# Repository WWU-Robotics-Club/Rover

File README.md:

# Rover

A robotic rover project.

See the wiki for more info: https://gitlab.cs.wallawalla.edu/robotics-club/Rover/-/wikis/home

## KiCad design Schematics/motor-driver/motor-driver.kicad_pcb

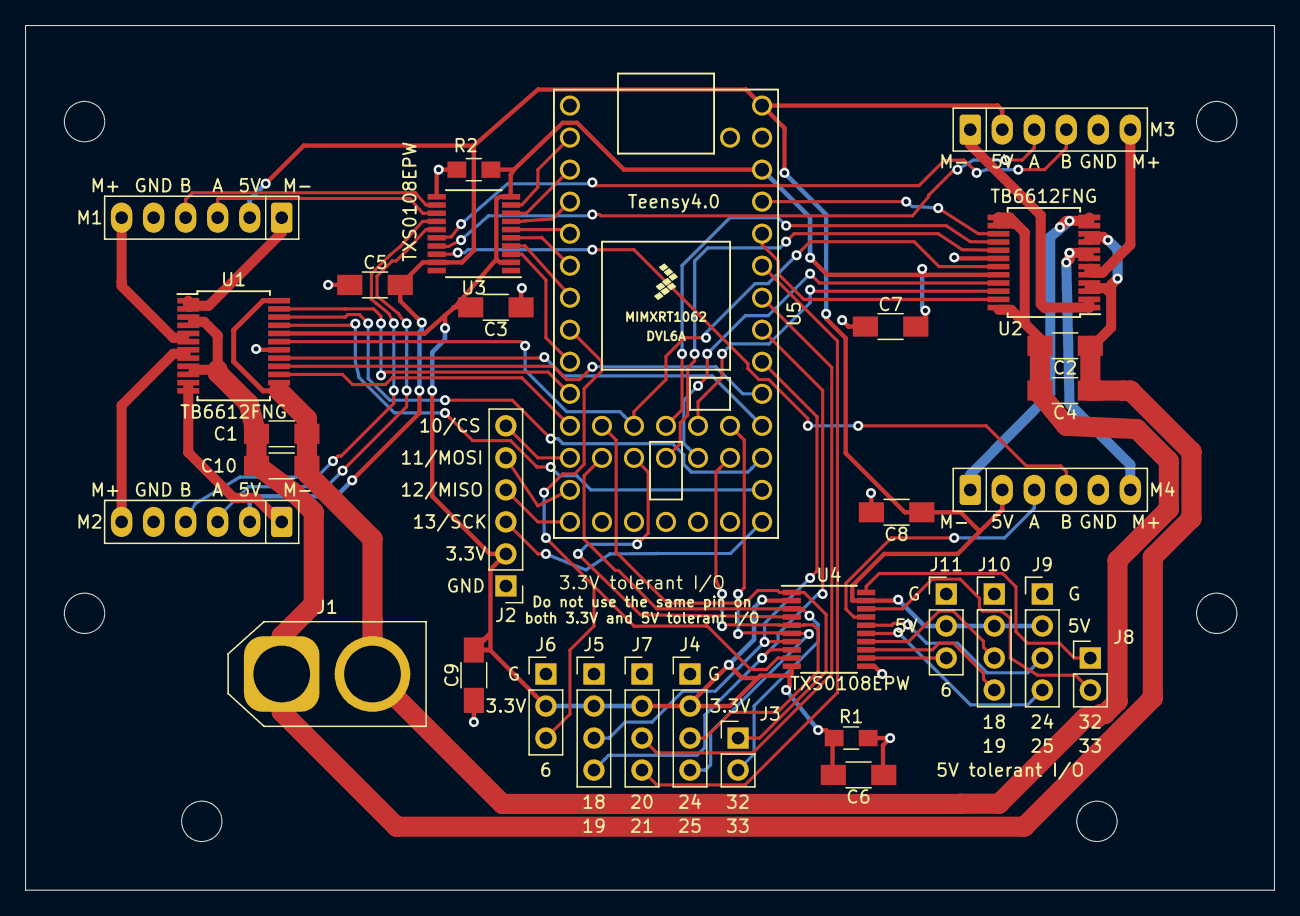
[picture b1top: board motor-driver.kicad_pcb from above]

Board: 2 copper layers, 99.1 x 68.6 mm, 32 parts (0 on the bottom side), 62 nets.

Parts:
C1, C2: 10uF; C_1206_HandSoldering
C3, C4, C5, C6, C7, C8, C9, C10: 0.1uF; C_1206_HandSoldering
J1: XT-60; AMASS_XT60-M_1x02_P7.20mm_Vertical
J2: SPI; SPI_3.3V
J3: 32-33 3.3V; 32-33_3.3V
J4: UART/I2C/PWM 3.3V; UART_I2C_PWM_3.3V
J5: I2C/Ain/PWM 3.3V; I2C_Ain_PWM_3.3V
J6: PWM/PPM 3.3V; PPM_PWM_3.3V
J7: UART/Ain; UART_Ain_3.3V
J8: 32-33 5V; 32-33_5V
J9: UART/I2C/PWM 5V; UART_I2C_PWM_5V
J10: I2C/Ain/PWM 5V; I2C_Ain_PWM_5V
J11: PWM/PPM 5V; PPM_PWM_5V
M1, M2, M3, M4: encoder-motor; Motor_Header_Pitch2.54mm
R1, R2: 47k; R_0805_HandSoldering
U1, U2: TB6612FNG; SSOP-24_5.3x8.2mm_Pitch0.65mm
U3, U4: TXS0108EPW; TSSOP-20_4.4x6.5mm_Pitch0.65mm
U5: Teensy4.0; Teensy40

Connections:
+3V3: C3.2, C6.2, C7.2, C9.2, J2.2, J4.2, J5.2, J6.2, J7.2, R1.1, R2.1, U1.20, U2.20, U3.2, U3.10, U4.2, U4.10, U5.31
+5V: C5.1, C8.1, J9.2, J10.2, J11.2, M1.2, M2.2, M3.2, M4.2, U3.19, U4.19, U5.33
+BATT: C1.2, C2.2, C4.2, C10.2, J1.2, U1.13, U1.14, U1.24, U2.13, U2.14, U2.24
-BATT: C1.1, C2.1, C4.1, C10.1, J1.1, U1.3, U1.4, U1.9, U1.10, U2.3, U2.4, U2.9, U2.10
/M1+: M1.6, U1.5, U1.6
/M1-: M1.1, U1.1, U1.2
/M2+: M2.6, U1.7, U1.8
/M2-: M2.1, U1.11, U1.12
/M3+: M3.6, U2.5, U2.6
/M3-: M3.1, U2.1, U2.2
/M4+: M4.6, U2.7, U2.8
/M4-: M4.1, U2.11, U2.12
GND: C3.1, C5.2, C6.1, C7.1, C8.2, C9.1, J2.1, J4.1, J5.1, J6.1, J7.1, J9.1, J10.1, J11.1, M1.5, M2.5, M3.5, M4.5, R1.2, R2.2, U1.18, U2.18, U3.11, U4.11, U5.1, U5.32
unnamed: J2.3, U5.20
unnamed: J2.4, U5.14
unnamed: J2.5, U5.13
unnamed: J2.6, U5.12
unnamed: J3.1, U4.1, U5.44
unnamed: J3.2, U4.3, U5.43
unnamed: J4.3, U4.5, U5.35
unnamed: J4.4, U4.6, U5.36
unnamed: J5.3, U4.7, U5.25
unnamed: J5.4, U4.8, U5.26
unnamed: J6.3, U4.9, U5.8
unnamed: J7.3, U5.27
unnamed: J7.4, U5.28
unnamed: J8.1, U4.20
unnamed: J8.2, U4.18
unnamed: J9.3, U4.16
unnamed: J9.4, U4.15
unnamed: J10.3, U4.14
unnamed: J10.4, U4.13
unnamed: J11.3, U4.12
unnamed: M1.3, U3.13
unnamed: M1.4, U3.12
unnamed: M2.3, U3.15
unnamed: M2.4, U3.14
unnamed: M3.3, U3.17
unnamed: M3.4, U3.16
unnamed: M4.3, U4.17
unnamed: M4.4, U3.18
unnamed: U1.15, U5.11
unnamed: U1.16, U5.24
unnamed: U1.17, U5.23
unnamed: U1.21, U5.21
unnamed: U1.22, U5.22
unnamed: U1.23, U5.10
unnamed: U2.15, U5.30
unnamed: U2.16, U5.40
unnamed: U2.17, U5.39
unnamed: U2.21, U5.37
unnamed: U2.22, U5.38
unnamed: U2.23, U5.29
unnamed: U3.3, U5.9
unnamed: U3.4, U5.7
unnamed: U3.5, U5.6
unnamed: U3.6, U5.5
unnamed: U3.7, U5.4
unnamed: U3.8, U5.3
unnamed: U3.9, U5.2
unnamed: U4.4, U5.41
STBY: U1.19, U2.19, U5.42

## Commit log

2019-10-19 Added ROS installation script
    #16
2019-10-20 Add Arduino and Teensyduino to install script
    #16
2019-10-20 Add ROS workspace and rover_core package
    #12
2019-11-07 Add Arduino script submodule and rosserial submodule
    #14
2019-12-19 Give usb port access to user
    Fixes some arduino errors
    #16
2020-01-10 WIP dockerfile and jenkins install script
    #16
2020-01-24 Add motor driver schematic
    #4
2020-01-24 Add teensy kicad symbol submodule
    #4
2020-01-24 Make library use relative url
    Change 3.3V to 5V
2020-01-26 Add motor driver pcb design
    Update schematics, add footprints, create pcb layout
    #4
2020-01-31 Add mounting holes to PCB
    Update submodule remote
    Remove files that should just be wiki pages
    #28, #16
2020-01-31 Add basic gitlab ci config
    #16
2020-01-31 Update docker image
2020-02-03 Update dockerfile and gitlab-ci config
    Also update submodule version
    #24
2020-02-03 Make gitlab clone submodules
    #24
2020-02-03 Fix linter errors
2020-02-05 Add docker-compose file for deployment
    Add start script
    Add roslaunch file to start nodes
    Add example publish/subscribe nodes
    Update dockerfile to copy in files needed for deployment
    #16
2020-02-07 Add realsense packages to dockerfile
    Add arduino deploy stage
    #34
2020-02-07 Attempt at adding realsense ros package
    cmake failing
    #12
2020-02-14 fix docker starting ROS
    #34
2020-02-14 Fix gitlab-ci syntax
    #34
2020-02-14 Fix roslaunch realsense error
    #39
2020-02-14 Add librealsense to install script
    #36
2020-02-28 Add pylint
    Add rosbridge to install scripts
    Add recommended extensions
2020-03-01 Start on web interface
    Add nodejs web server and websocket relay to rosbridge
    Add rosbridge to launchfile
    Add nginx ssl proxy
    Add example roslibjs website
    Split usb portions of docker-compose into its own file
2020-03-01 Add joystick to webpage
2020-03-04 Add MIT license
2020-03-04 Replace webpage filler text, add ros topic and node list
    Update formatting
    #38
2020-03-05 Don't install debug symbols, mount all serial devices
    might change later but if the motor controleller wasn't plugged in it would error
2020-03-06 Added the Topics and Nodes
2020-03-12 Start updating to use teensy 4.0
    Need to add level shifters
2020-03-13 Uploading Rover Branch
2020-03-13 Fix ROS publisher
2020-03-13 Give ROS container privileged mode. Maybe usb permissions could work instead
2020-03-15 Add some more footprints
2020-03-15 Update schematic and start on PCB layout
2020-03-16 Finish updating motor driver PCB for Teensy 4.0
2020-05-07 Add gerber files and update arduino code
2020-05-08 ROS stereo script using the Realsense Topics
2020-05-12 Update node image and motor control submodule
2020-05-13 Fix cpplint errors
2020-05-13 Fix typo
2020-05-13 Update webpage to connect to the correct topic and have reasonable joystick outputs
2020-05-20 Make Websocket Connection more reliable
    Update webpage text
    Hopefully fix cpplint errors
    Add npm install to the node dockerfile
2020-05-21 Add joystick modes to webpage
    Make server side websocket auto-reconnect to ROS
    Update motor controller submodule
2020-06-05 Created AprilTags continuous detector code and Updates for comments for stereo camera
2020-06-12 Add files for 3d printing
    Gave schematic a title and saved a schematic PDF
2020-06-12 Update PlatformIO auto-deploy to only try to deploy one environment
2020-06-18 Added comments for AprilTag and Stereo Code. Also checked style guide with PEP8. Added new nodes for these two files to launch file
2020-06-18 Revert "Added comments for AprilTag and Stereo Code. Also checked style guide with PEP8. Added new nodes for these two files to launch file"
    This reverts commit ccf181326e58502b45c9d789daddef731f440660.
2020-06-18 Updated rover.lauch with new nodes from these files. Added comments for AprilTag and Stereo Code. Used PEP8 to check style of code.
2020-08-10 Fix typo
    Stop using find command because it always returns ok even if build fails
2021-05-30 Bump ws from 7.2.1 to 7.4.6 in /node
    Bumps [ws](https://github.com/websockets/ws) from 7.2.1 to 7.4.6.
    - [Release notes](https://github.com/websockets/ws/releases)
    - [Commits](https://github.com/websockets/ws/compare/7.2.1...7.4.6)
2022-12-07 Bump qs and express in /node
    Bumps [qs](https://github.com/ljharb/qs) to 6.11.0 and updates ancestor dependency [express](https://github.com/expressjs/express). These dependencies need to be updated together.
    Updates `qs` from 6.7.0 to 6.11.0
    - [Release notes](https://github.com/ljharb/qs/releases)
    - [Changelog](https://github.com/ljharb/qs/blob/main/CHANGELOG.md)
    - [Commits](https://github.com/ljharb/qs/compare/v6.7.0...v6.11.0)
    Updates `express` from 4.17.1 to 4.18.2
2022-12-13 Bump express from 4.17.1 to 4.17.3 in /node
    Bumps [express](https://github.com/expressjs/express) from 4.17.1 to 4.17.3.
    - [Release notes](https://github.com/expressjs/express/releases)
    - [Changelog](https://github.com/expressjs/express/blob/master/History.md)
    - [Commits](https://github.com/expressjs/express/compare/4.17.1...4.17.3)
    ---
    updated-dependencies:
